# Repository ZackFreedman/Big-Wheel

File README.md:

# Big Wheel
 3D-printed video control surface

Slapped together in a weekend by Zack Freedman of Voidstar Lab for [a YouTube video! Check it out!](https://www.youtube.com/watch?v=72a85tWOJVY)

Materials:
- 1x each of:
    - Big Ass-Wheel.stl
    - Body.stl
    - Wheel Insert.stl
- 1x of either of the following:
    - One print of Waffle Baseplate Combo.stl
    - One print of Support Waffle.stl and one laser-cut Big Wheel Baseplate.ai
- 7x 10mm M2.5 screws
- 6x M2.5 heat-set inserts, nominal 5mm length
- 1x M2.5 nut
- 14x Cherry MX-compatible keyswitches
- 14x keycaps for keyswitches
- 14x rectifier diodes, such as the 1N4004
- 4x PEC12-compatible rotary encoders with pushbutton, 15mm flatted shaft preferred
- 3x encoder knobs, max. diameter 22mm
- 6x rubber feet, thicker than the head of the M2.5 screws
- 1x Teensy LC, Teensy 3.x, or Teensy 4.0
- Zap-a-Gap or other adhesive that can bond your 3D-printing material
- Lots of wire and heatshrink

Instructions:
1. [Watch video](https://www.youtube.com/watch?v=72a85tWOJVY) to see construction overview
2. Fabricate 3D-printed and laser-cut parts
3. If using laser-cut Big Wheel Baseplate, glue Support Waffle onto the etched side of the Baseplate.
4. Snap keyswitches and encoders into Body
5. Using wiring diagram, build switch matrix. Take care to route wires away from surface that contacts Support Waffle.
6. Connect switch matrix and encoders to Teensy. Take care to leave extra wire!
7. Slide Teensy into its rails. It should fit snugly - if it's loose, add a bit of electrical tape to tighten things up.
8. Connect to computer, load firmware, and test
9. Using a soldering iron, apply heat-set inserts to the bosses on the Body.
10. Mount Waffle and Baseplate combo to the Body using the screws.
11. Apply rubber feet to Baseplate.
12. Slip nut into slot on Big Ass-Wheel and insert screw through side of wheel.
13. Mount Big Ass-Wheel on center encoder and tighten screw. It should turn smoothly but not wobble.
14. Glue Wheel Insert onto Big Ass-Wheel.
15. Mount remaining encoder knobs and keycaps.
16. If desired, modify firmware to bind your preferred commands to the controls.
17. Let Zack know you built the project!

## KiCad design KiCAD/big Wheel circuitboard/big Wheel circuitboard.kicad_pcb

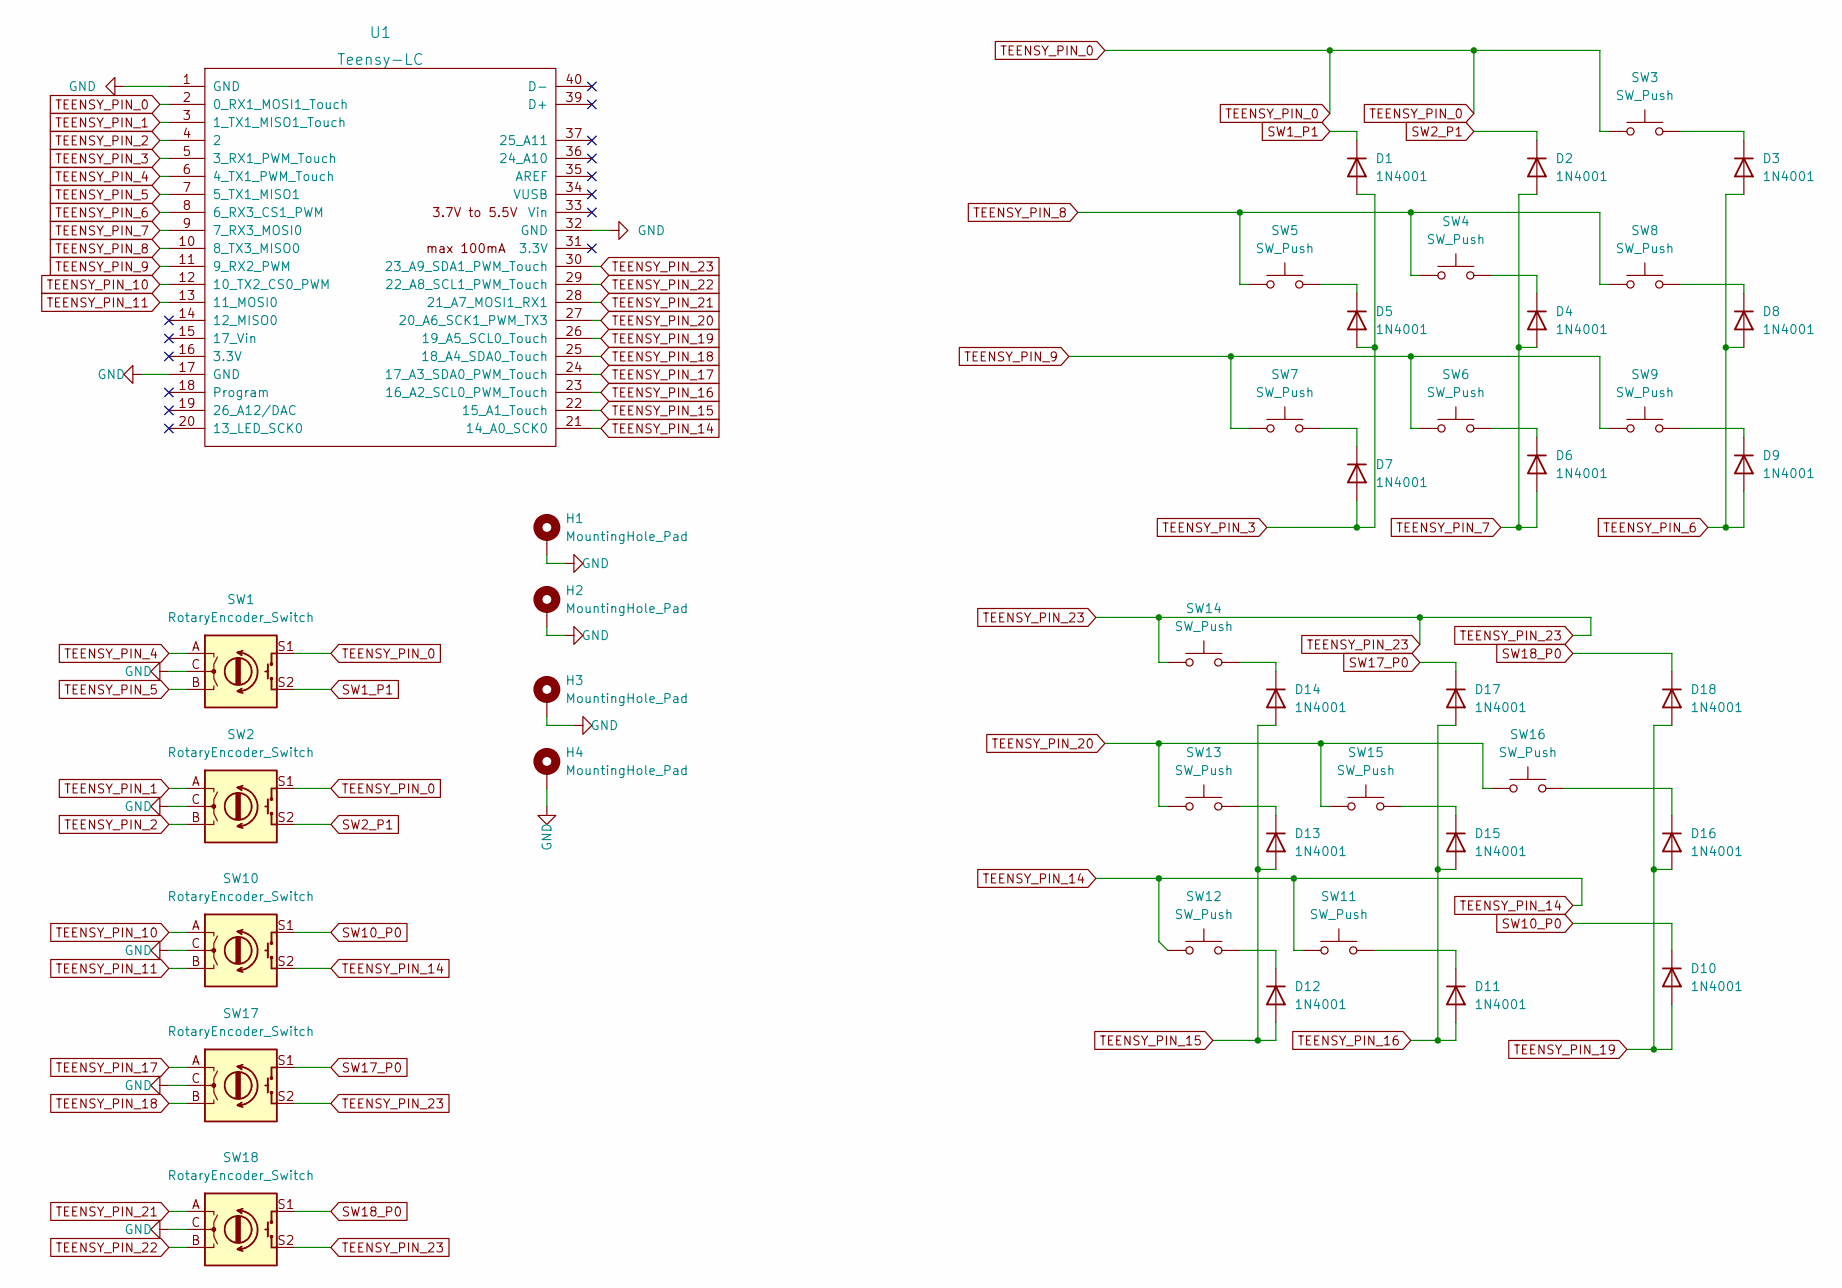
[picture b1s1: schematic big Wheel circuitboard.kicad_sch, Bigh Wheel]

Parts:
D1, D2, D3, D4, D5, D6, D7, D8, D9, D10, D11, D12, D13, D14, D15, D16, D17, D18: 1N4001; D_DO-41_SOD81_P10.16mm_Horizontal
H1, H2, H3, H4: MountingHole_Pad; MountingHole_3mm_Pad
SW1, SW2, SW10, SW17, SW18: RotaryEncoder_Switch; RotaryEncoder_Alps_EC11E-Switch_Vertical_H20mm
SW3, SW4, SW5, SW6, SW7, SW8, SW9, SW11, SW12, SW13, SW14, SW15, SW16: SW_Push; SW_Hybrid_Cherry_MX_Alps
U1: Teensy-LC; Teensy_LC

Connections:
GND: H1.1, H2.1, H3.1, H4.1, SW1.C, SW2.C, SW10.C, SW17.C, SW18.C, U1.1 (GND), U1.17 (GND), U1.32 (GND)
unnamed: D3.1 (K), SW3.2
unnamed: D5.1 (K), SW5.2
unnamed: D6.1 (K), SW6.2
unnamed: D7.1 (K), SW7.2
unnamed: D8.1 (K), SW8.2
unnamed: D9.1 (K), SW9.2
unnamed: D12.1 (K), SW12.2
unnamed: D13.1 (K), SW13.2
unnamed: D14.1 (K), SW14.2
unnamed: D4.1 (K), SW4.2
unnamed: D11.1 (K), SW11.2
unnamed: D15.1 (K), SW15.2
unnamed: D16.1 (K), SW16.2
SW1_P1: D1.1 (K), SW1.S2
SW2_P1: D2.1 (K), SW2.S2
SW10_P0: D10.1 (K), SW10.S1
SW17_P0: D17.1 (K), SW17.S1
SW18_P0: D18.1 (K), SW18.S1
TEENSY_PIN_0: SW1.S1, SW2.S1, SW3.1, U1.2 (0_RX1_MOSI1_Touch)
TEENSY_PIN_1: SW2.A, U1.3 (1_TX1_MISO1_Touch)
TEENSY_PIN_2: SW2.B, U1.4 (2)
TEENSY_PIN_3: D1.2 (A), D5.2 (A), D7.2 (A), U1.5 (3_RX1_PWM_Touch)
TEENSY_PIN_4: SW1.A, U1.6 (4_TX1_PWM_Touch)
TEENSY_PIN_5: SW1.B, U1.7 (5_TX1_MISO1)
TEENSY_PIN_6: D3.2 (A), D8.2 (A), D9.2 (A), U1.8 (6_RX3_CS1_PWM)
TEENSY_PIN_7: D2.2 (A), D4.2 (A), D6.2 (A), U1.9 (7_RX3_MOSI0)
TEENSY_PIN_8: SW4.1, SW5.1, SW8.1, U1.10 (8_TX3_MISO0)
TEENSY_PIN_9: SW6.1, SW7.1, SW9.1, U1.11 (9_RX2_PWM)
TEENSY_PIN_10: SW10.A, U1.12 (10_TX2_CS0_PWM)
TEENSY_PIN_11: SW10.B, U1.13 (11_MOSI0)
TEENSY_PIN_14: SW10.S2, SW11.1, SW12.1, U1.21 (14_A0_SCK0)
TEENSY_PIN_15: D12.2 (A), D13.2 (A), D14.2 (A), U1.22 (15_A1_Touch)
TEENSY_PIN_16: D11.2 (A), D15.2 (A), D17.2 (A), U1.23 (16_A2_SCL0_PWM_Touch)
TEENSY_PIN_17: SW17.A, U1.24 (17_A3_SDA0_PWM_Touch)
TEENSY_PIN_18: SW17.B, U1.25 (18_A4_SDA0_Touch)
TEENSY_PIN_19: D10.2 (A), D16.2 (A), D18.2 (A), U1.26 (19_A5_SCL0_Touch)
TEENSY_PIN_20: SW13.1, SW15.1, SW16.1, U1.27 (20_A6_SCK1_PWM_TX3)
TEENSY_PIN_21: SW18.A, U1.28 (21_A7_MOSI1_RX1)
TEENSY_PIN_22: SW18.B, U1.29 (22_A8_SCL1_PWM_Touch)
TEENSY_PIN_23: SW14.1, SW17.S2, SW18.S2, U1.30 (23_A9_SDA1_PWM_Touch)

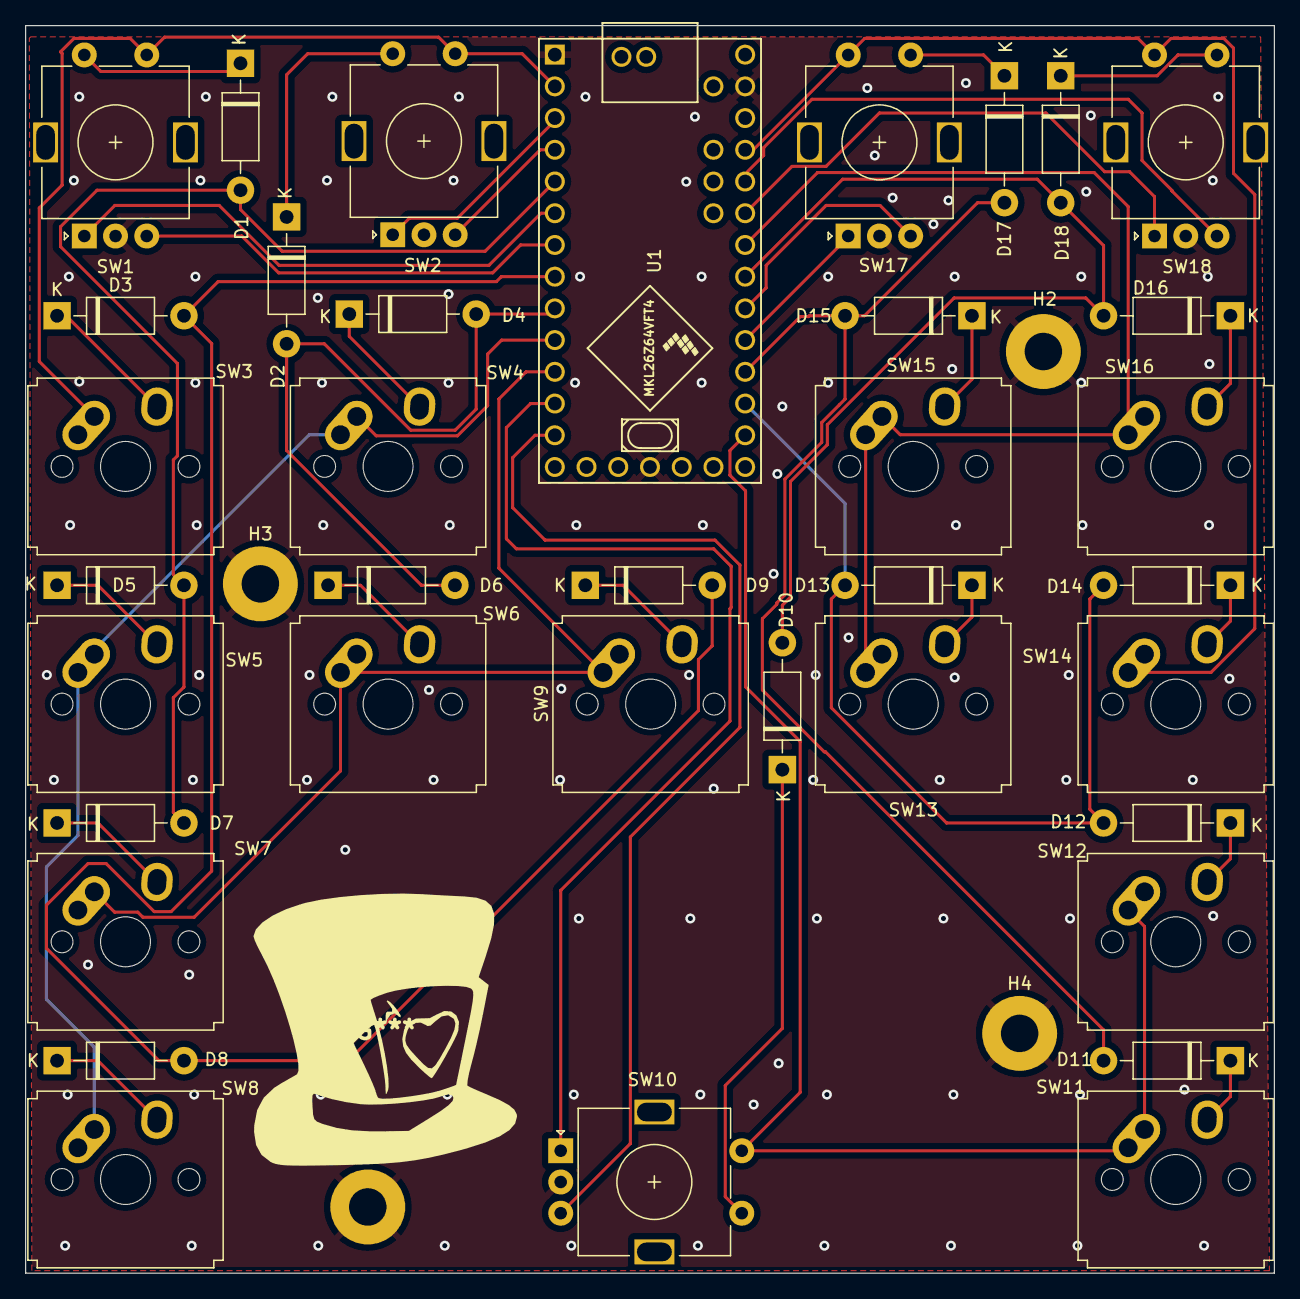
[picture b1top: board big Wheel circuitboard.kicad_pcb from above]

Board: 2 copper layers, 100.0 x 99.9 mm, 41 parts (0 on the bottom side), 41 nets.

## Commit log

2020-09-23 Initial commit
    What do you call a baby turkey?
    A goblet.
2020-10-05 Firmware improvements
    - Changed ALT key to GUI
    - Improved shuttle lock reliability
    - Refactored matrix-reading code
    - Added debouncing to matrix
    - Refactored knob reading code
2020-10-05 Cleaned up firmware after refactor
2020-10-05 Added documentation
    - Added URL's to sketch
    - Added BOM and instructions to Readme
    - Added wiring diagram
2020-11-19 Fixed error in wiring diagram
    BOTTOM_KNOB_B was labeled as Pin 10, should be Pin 14. Thanks to @CarlesM on Twitter for spotting.
2021-04-09 Update Big_Wheel_Macro_Pad_Firmware.ino
    Changed the max value that the actionIndex can reach from 6, to 5.
    This would cause a crash if more than 6 actions during a frame since the code would try to write a seventh value to a 6 element array
2022-06-01 Previous to major shuttle rework for davinci
2022-06-02 refactored the firmware
2022-06-04 added circuit board stuff
2022-06-04 Added build files for first order
